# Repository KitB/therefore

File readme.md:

# Therefore Mechanical Keyboard

Therefore is a from-scratch ergodox clone focussing on ease of use between
multiple computers in multiple locations and firmware written in Python for ease
of customization.

### Design goals:

* USB-C, BLE, NRF24L01 dongle, and possibly Logitech Unifying Receiver
  connectivity
* Wireless split alongside TRRS as an option
* Compact and low-profile, designed for portability ("portodox" was a candidate
  name)
* Carrying case or magnetic snap-together of the halves
* Either easy-to-source parts (e.g. adafruit and bog-standard components) or
  a single PCB with everything on it manufactured by e.g. JLCPCB.
  
### Non-goals:

* Low latency: this is not a gaming keyboard; latency between split halves is
  important for avoiding transposition errors though.
* USB Hub: Sadly not possible over the wireless protocols.
* Adjustments to normal ergodox layout: In particular no adjustments will be
  made in the name of compactness; the goal is to make it as compact as possible
  within the layout of the normal ergodox.

 ## State of affairs
 I am typing this on a therefore made out of PCBs manufactured by JLCPCB with
 a case I 3d printed (and then cut up a little to make a bigger hole for USB
 cables). Each half has a Adafruit Feather NRF52840 and a hand-wired TRRS
 connector. It is very much a prototype but I have been typing on this
 keyboard alone for months now.
 
 Code for fully wireless operation is present and functional but latency between
 halves ruins it; I don't think this is inherent in BLE, just present in this
 implementation.
 
 ## License
 The firmware is BSD 3-clause licensed (see [firmware/python/LICENSE ](firmware/python/LICENSE))
 but the hardware is currently all-rights-reserved.
 It will in future be open source or at least free for non-commercial use.

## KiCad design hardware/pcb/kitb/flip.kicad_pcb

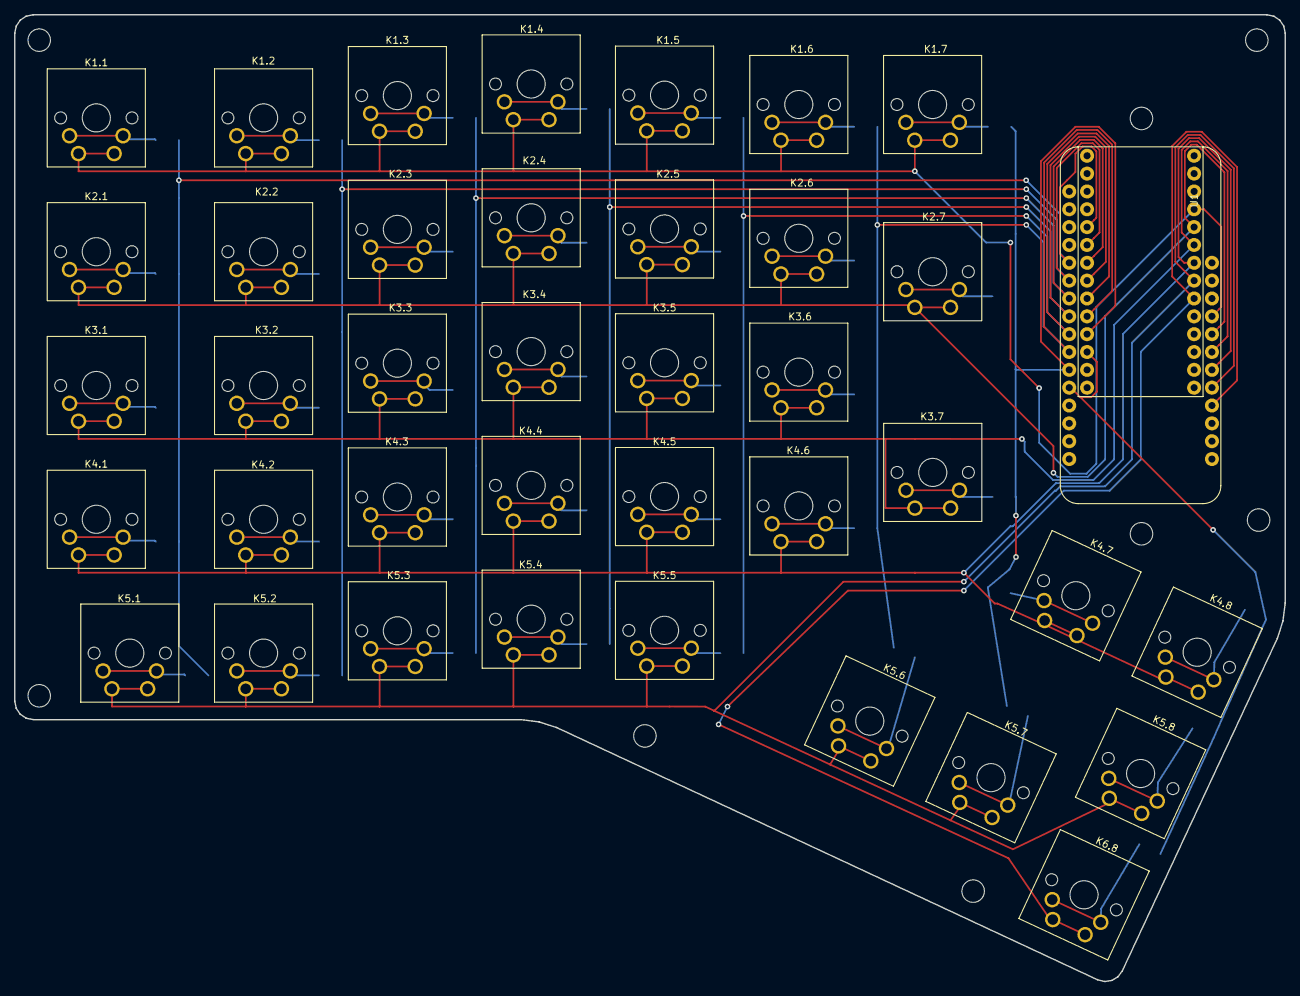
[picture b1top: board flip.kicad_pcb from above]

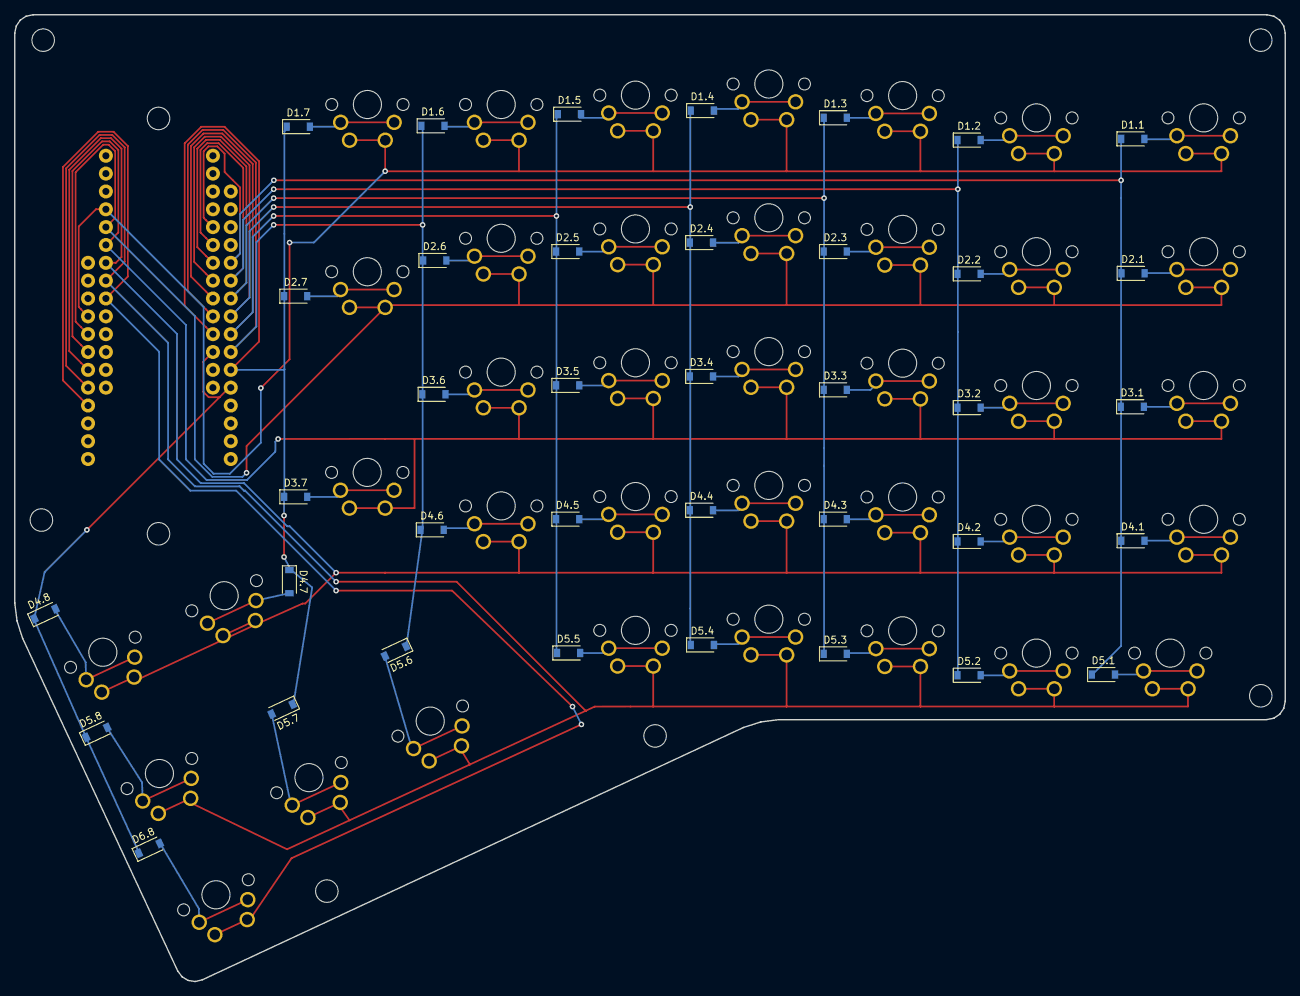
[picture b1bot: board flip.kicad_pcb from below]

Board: 2 copper layers, 180.9 x 137.6 mm, 77 parts (38 on the bottom side), 52 nets.

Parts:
D1.1, D1.2, D1.3, D1.4, D1.5, D1.6, D1.7, D2.1, D2.2, D2.3, D2.4, D2.5, D2.6, D2.7, D3.1, D3.2, D3.3, D3.4, D3.5, D3.6, D3.7, D4.1, D4.2, D4.3, D4.4, D4.5, D4.6, D4.7, D4.8, D5.1, D5.2, D5.3, D5.4, D5.5, D5.6, D5.7, D5.8, D6.8: D; D_SOD-123
K1.1, K2.1, K3.1, K4.1: switch; SW_Cherry_MX1A_1.50u_PCB_ra
K1.2, K1.3, K1.4, K1.5, K1.6, K1.7, K2.2, K2.3, K2.4, K2.5, K2.6, K3.2, K3.3, K3.4, K3.5, K3.6, K4.2, K4.3, K4.4, K4.5, K4.6, K4.7, K4.8, K5.1, K5.2, K5.3, K5.4, K5.5, K5.8, K6.8: switch; SW_Cherry_MX1A_1.00u_PCB_ra
K2.7, K3.7: switch; SW_Cherry_MX1A_1.50u_PCB
K5.6, K5.7: switch; SW_Cherry_MX1A_2.00u_Vertical_PCB
U1: MCU; mcu

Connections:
unnamed: D1.1.1, D2.1.1, D3.1.1, D4.1.1, D5.1.1, U1.A0
unnamed: D1.1.2, K1.1.2
unnamed: D1.2.1, D2.2.1, D3.2.1, D4.2.1, D5.2.1, U1.A1
unnamed: D1.2.2, K1.2.2
unnamed: D1.3.1, D2.3.1, D3.3.1, D4.3.1, D5.3.1, U1.A2
unnamed: D1.3.2, K1.3.2
unnamed: D1.4.1, D2.4.1, D3.4.1, D4.4.1, D5.4.1, U1.A3
unnamed: D1.4.2, K1.4.2
unnamed: D1.5.1, D2.5.1, D3.5.1, D4.5.1, D5.5.1, U1.A4
unnamed: D1.5.2, K1.5.2
unnamed: D1.6.1, D2.6.1, D3.6.1, D4.6.1, D5.6.1, U1.A5
unnamed: D1.6.2, K1.6.2
unnamed: D1.7.1, D2.7.1, D3.7.1, D4.7.1, D5.7.1, U1.SCK
unnamed: D1.7.2, K1.7.2
unnamed: D2.1.2, K2.1.2
unnamed: D2.2.2, K2.2.2
unnamed: D2.3.2, K2.3.2
unnamed: D2.4.2, K2.4.2
unnamed: D2.5.2, K2.5.2
unnamed: D2.6.2, K2.6.2
unnamed: D2.7.2, K2.7.2
unnamed: D3.1.2, K3.1.2
unnamed: D3.2.2, K3.2.2
unnamed: D3.3.2, K3.3.2
unnamed: D3.4.2, K3.4.2
unnamed: D3.5.2, K3.5.2
unnamed: D3.6.2, K3.6.2
unnamed: D3.7.2, K3.7.2
unnamed: D4.1.2, K4.1.2
unnamed: D4.2.2, K4.2.2
unnamed: D4.3.2, K4.3.2
unnamed: D4.4.2, K4.4.2
unnamed: D4.5.2, K4.5.2
unnamed: D4.6.2, K4.6.2
unnamed: D4.7.2, K4.7.2
unnamed: D4.8.1, D5.8.1, D6.8.1, U1.MO
unnamed: D4.8.2, K4.8.2
unnamed: D5.1.2, K5.1.2
unnamed: D5.2.2, K5.2.2
unnamed: D5.3.2, K5.3.2
unnamed: D5.4.2, K5.4.2
unnamed: D5.5.2, K5.5.2
unnamed: D5.6.2, K5.6.2
unnamed: D5.7.2, K5.7.2
unnamed: D5.8.2, K5.8.2
unnamed: D6.8.2, K6.8.2
unnamed: K1.1.1, K1.2.1, K1.3.1, K1.4.1, K1.5.1, K1.6.1, K1.7.1, U1.13
unnamed: K2.1.1, K2.2.1, K2.3.1, K2.4.1, K2.5.1, K2.6.1, K2.7.1, U1.12
unnamed: K3.1.1, K3.2.1, K3.3.1, K3.4.1, K3.5.1, K3.6.1, K3.7.1, U1.11
unnamed: K4.1.1, K4.2.1, K4.3.1, K4.4.1, K4.5.1, K4.6.1, K4.7.1, K4.8.1, U1.10
unnamed: K5.1.1, K5.2.1, K5.3.1, K5.4.1, K5.5.1, K5.6.1, K5.7.1, K5.8.1, U1.9
unnamed: K6.8.1, U1.7,6

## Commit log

2020-02-27 Make case.scad render the default as an example
    rather than just being broken.
2020-02-27 Add basic USB firmware
    next up: BLE HID
    then: auto switch
2020-02-27 Modularise the current firmware
2020-02-27 Add BLE support
    that was way too easy
2020-02-28 Largely working auto-switch between USB and BLE
2020-02-29 Full two-hand with BLE bridge
    Doesn't auto-switch between usb and ble, that shit didn't work very
    well.
2020-02-29 Layers
2020-03-04 Layout fixes and make space for potential alternative firmwares
2020-03-04 Switch to something that starts to look like an enum for state
2020-03-04 Add python gitignore
2020-03-09 Release keys on layer change
    The scenarios in which this is insufficient are unlikely.
2020-03-28 Add screwless case
2020-04-22 Add source files for current PCB
    Maybe? I'm not sure exactly how much is necessary.
2020-04-24 Update key layout to match actual PCB
2020-04-24 Add first finished screwy case
    Planning some changes but I've actually produced this case and it works.
    Mostly.
2020-10-24 up-to-date firmware
2020-10-30 Use UART over TRRS for the time being
    BLE latency is too high, transposition errors abound. Might just be to
    do with circuitpython's BLE implementation.
2020-10-30 Allow keyboard to function one-handed
2021-03-25 Add janky layer -> layer implementation
    e.g. going to a new layer when you're already on a layer
    I actually wrote this months ago and am about to commit a better
    implementation.
2021-03-25 Add a spacebar to left hand
    moves alt which will take a little getting used to but allows gaming
    without changing layer.
2021-03-25 Add currently-unused-but-tested layout handling
    This is the better layer implementation. Still need to hook it up to the
    rest of the firmware.
2021-03-26 Hook up new layout handling
    Also adds media controls and key sequences.
2021-03-26 Add BSD license to firmware/python
    Applies only to the python firmware; hardware is all-rights-reserved for
    the time being (while I consider potential commercialization options).
    The hardware will definitely be free for non-commercial uses in future.
2021-03-26 Add a readme
    finally
